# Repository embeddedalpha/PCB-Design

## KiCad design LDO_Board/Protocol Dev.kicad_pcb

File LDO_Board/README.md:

# LDO-Board

#1 View 1

#2 View 2

#3 View 3

#4 F.Cu

#5 B.Cu

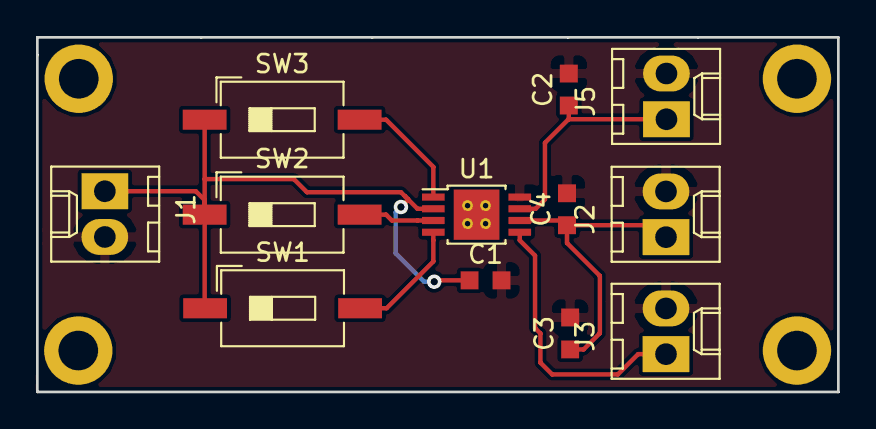
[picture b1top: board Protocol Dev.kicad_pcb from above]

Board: 2 copper layers, 44.5 x 19.7 mm, 12 parts (0 on the bottom side), 8 nets.

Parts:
C1, C2, C3, C4: C_Small; C_0603_1608Metric_Pad0.99x1.00mm_HandSolder
J1, J2, J3, J5: Conn_01x02; Molex_KK-6410-02_02x2.54mm_Straight
SW1, SW2, SW3: SW_Push; SW_DIP_SPSTx01_Slide_6.7x4.1mm_W8.61mm_P2.54mm_LowProfile
U1: MIC5356-SGYMME; MSOP-8-1EP_3x3mm_P0.65mm_EP2.54x2.8mm_ThermalVias

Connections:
+1V5: C3.1, C4.1, J2.1, U1.6
+1V8: C2.1, J5.1, U1.7
+3V3: J3.1, U1.5
/EN1: SW1.2, U1.4
/EN2: SW2.2, U1.3
/EN3: SW3.2, U1.1
/IN: C1.1, J1.1, SW1.1, SW2.1, SW3.1, U1.2
GND: C1.2, C2.2, C3.2, C4.2, J1.2, J2.2, J3.2, J5.2, U1.8

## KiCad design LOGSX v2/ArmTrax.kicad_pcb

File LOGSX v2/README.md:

<H1> LOGSX v2: Low Power Logistic Tracker </H1>

<H4> Overview </H4>

<H4> 1: </H4>

<H4> 2: </H4>

<H4> 3: </H4>

<H4> 4: </H4>

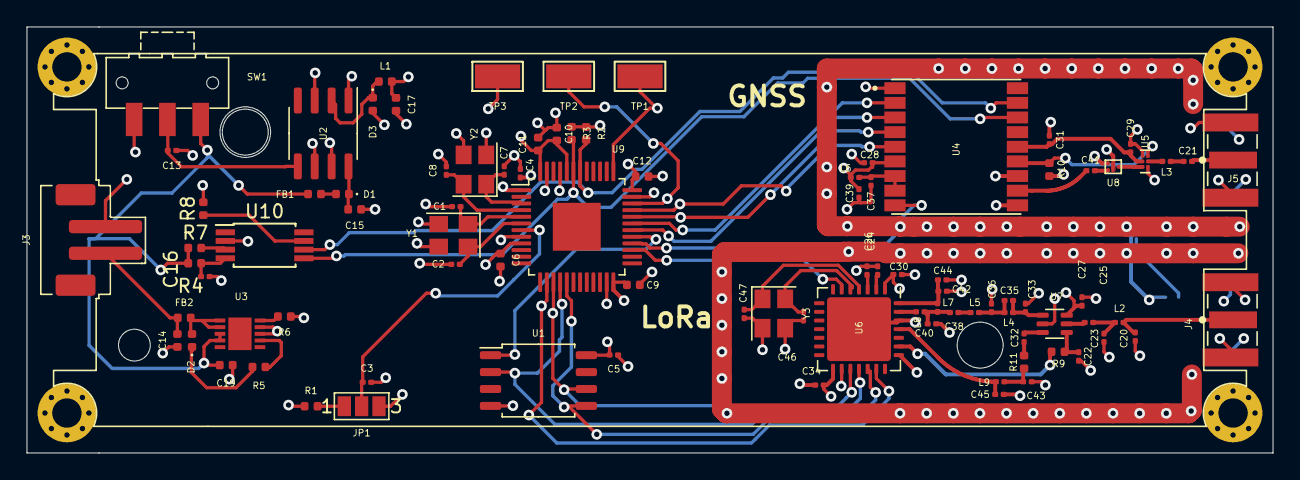
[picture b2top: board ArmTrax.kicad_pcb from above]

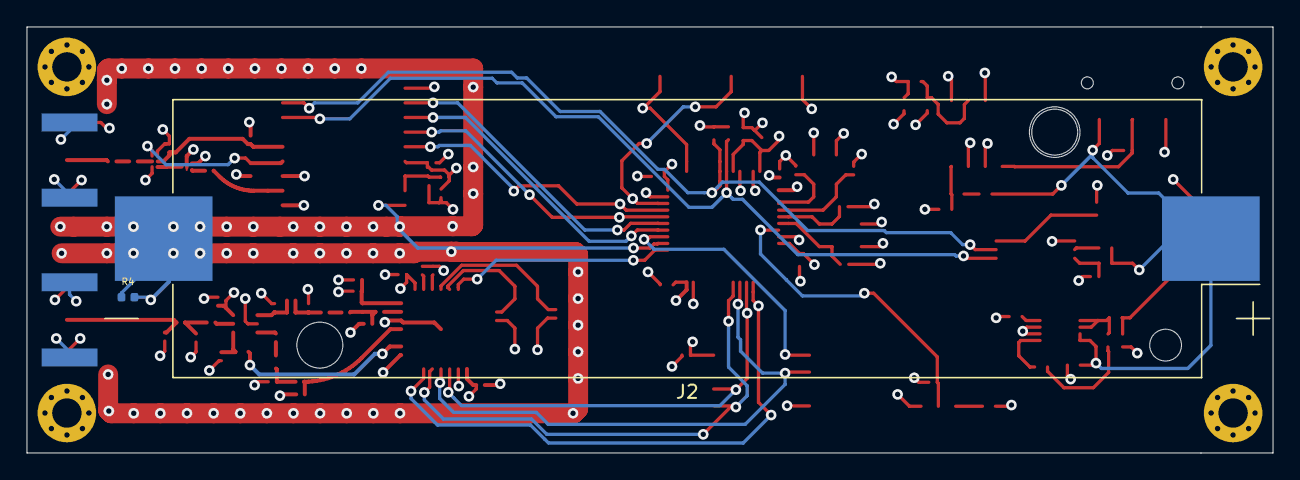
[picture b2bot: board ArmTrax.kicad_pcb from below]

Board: 4 copper layers, 93.6 x 32.0 mm, 94 parts (2 on the bottom side), 63 nets.

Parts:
C1, C2, C3, C4, C5, C46, C47: 2.2pF; C_0201_0603Metric
C6, C15: 1uF; C_0402_1005Metric
C7, C8: 1pF; C_0201_0603Metric
C9, C10, C11, C12: 2.2pF; C_0402_1005Metric
C13, C16, C22, C27, C29: 1nF; C_0201_0603Metric
C14, C19: 22pF; C_0402_1005Metric
C17: 330uF; C_0402_1005Metric
C20, C23, C25, C33, C35, C36, C38, C40, C42, C43, C44, C45: X; C_0201_0603Metric
C21, C32, C41: 120pF; C_0201_0603Metric
C24, C26, C30, C34: 100nF; C_0201_0603Metric
C28, C31, C37, C39: 56pF; C_0201_0603Metric
D1: D_Small; D_0402_1005Metric
D2: LED; LED_0402_1005Metric
D3: 1N5822; D_0402_1005Metric
FB1, FB2: 100MHz; L_0402_1005Metric
J2: BATTERY CONN; BatteryHolder_Keystone_1042_1x18650
J3: POWER IN; JST_PH_B2B-PH-SM4-TB_1x02-1MP_P2.00mm_Vertical
J4, J5: SMA_Edge; SMA-J-P-H-ST-EM1
JP1: SolderJumper_3_Open; SolderJumper-3_P1.3mm_Open_Pad1.0x1.5mm_NumberLabels
L1: 330uH; L_0402_1005Metric
L2, L4, L5, L7, L8, L9: X; L_0201_0603Metric
L3: 5nF; L_0201_0603Metric
L6: 27nH; L_0201_0603Metric
R1: 1K7; R_0402_1005Metric
R2, R3: 4.7K; R_0402_1005Metric
R4: 500; R_0402_1005Metric
R4#2: R_Small; R_0402_1005Metric
R5, R6, R7, R8, R9: 1K; R_0402_1005Metric
R10: 10K; R_0402_1005Metric
R11: 0; R_0402_1005Metric
SW1: SW_SPDT; SW_SPDT_CK-JS102011SAQN
TP1, TP2, TP3: TestPoint; TestPoint_Keystone_5015_Micro-Minature
U1: W25Q32JVSS; SOIC-8_5.23x5.23mm_P1.27mm
U2: LT1129-3.3_SO8; SOIC-8_3.9x4.9mm_P1.27mm
U3: MCP73113_4; MCP73113
U4: TESEO-LIV3F
U5: BGA725L6E6327FTSA1
U6: SX1273; QFN-28-1EP_6x6mm_P0.65mm_EP4.8x4.8mm
U7: PE4259; PE4259_sc70
U8: B4327
U9: STM32F103C8Tx; LQFP-48-1EP_7x7mm_P0.5mm_EP3.6x3.6mm
U10: DS2782; TSSOP-8_4.4x3mm_P0.65mm
Y1, Y2, Y3: Crystal_GND23; Crystal_SMD_Abracon_ABM8G-4Pin_3.2x2.5mm

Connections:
1PPS: U4.4, U9.32
+3V3: C4.2, C5.2, C6.1, C9.1, C10.1, C11.1, C12.1, C17.1, C27.2, C28.2, C30.2, C34.2, C39.2, L1.2, L6.2, R1.1, R2.1, R3.1, U1.8, U2.1, U4.6, U6.1, U6.15, U7.6, U9.1, U9.9, U9.24, U9.36, U9.44, U9.48
ANT_OFF: R10.1, U4.13, U5.6
BATTERY: C19.1, FB1.2, J2.1, R4.2, R7.2, SW1.1, U3.3, U3.4
FLASH_NSS: U1.1, U9.29
GND: C1.2, C2.2, C3.2, C4.1, C5.1, C6.2, C7.2, C8.2, C9.2, C10.2, C11.2, C12.2, C13.2, C14.2, C15.2, C16.2, C17.2, C19.2, C20.1, C22.2, C23.2, C24.2, C26.2, C27.1, C28.1, C29.1, C30.1, C31.1, C33.1, C34.1, C36.1, C37.1, C39.1, C40.2, C42.2, C43.1, C44.2, C45.1, C46.2, C47.2, D3.2, J2.2, J3.2, J4.2_1, J4.2_2, J4.3_1, J4.3_2, J5.2_1, J5.2_2, J5.3_1, J5.3_2, JP1.3, R4#2.1, R4#2.2, R6.1, R8.2, R10.2, SW1.3, TP3.1, U1.4, U2.3, U2.6, U2.7, U3.8, U3.9, U4.1, U4.9, U4.10, U4.12, U5.1, U5.4, U6.16, U6.22, U6.26, U6.29, U7.2, U8.2, U8.3, U8.5, U9.8, U9.23, U9.28, U9.35, U9.47, U10.2, Y1.2, Y1.3, Y2.2, Y2.3, Y3.2, Y3.3
LoRa_NSS: U6.20, U9.14
LoRa_RESET: U6.6, U9.27
MISO: U1.2, U6.18, U9.16
MOSI: U1.5, U6.19, U9.17
unnamed: C3.1, JP1.2, U9.7
unnamed: C13.1, SW1.2, U2.5
unnamed: C14.1, FB2.2, J3.1
unnamed: C15.1, D1.1, U2.8
unnamed: C16.1, R4.1, U10.4
unnamed: C20.2, J4.1, L2.1
unnamed: C21.1, L3.1
unnamed: C21.2, J5.1
unnamed: C22.1, R9.1, U7.4
unnamed: C23.1, C25.2, L2.2
unnamed: C24.1, U6.2
unnamed: C25.1, U7.5
unnamed: C26.1, U6.3
unnamed: C32.1, U7.3
unnamed: C32.2, R11.2
unnamed: C33.2, C35.1, L4.1, U7.1
unnamed: C35.2, C36.2, L4.2, L5.1
unnamed: C37.2, L6.1, U4.7, U4.8
unnamed: C38.1, L5.2
unnamed: C38.2, C40.1, L7.1, L8.1
unnamed: C41.2, U8.4
unnamed: C43.2, L9.1, R11.1
unnamed: D1.2, FB1.1
unnamed: D2.1, R5.1
unnamed: D2.2, FB2.1, U3.1, U3.2
unnamed: D3.1, L1.1, U2.2
unnamed: JP1.1, R1.2
unnamed: L3.2, U5.5
unnamed: R5.2, U3.7
unnamed: R6.2, U3.10
unnamed: R7.1, U10.3
unnamed: U5.3, U8.1
OSC32_IN: C7.1, U9.3, Y2.1
OSC32_OUT: C8.1, U9.4, Y2.4
OSC_IN: C1.1, U9.5, Y1.1
OSC_OUT: C2.1, U9.6, Y1.4
PA_BOOST: L8.2, U6.27
RFI: C45.2, L9.2, U6.25
RF_IN: C41.1, U4.11
RX: U4.3, U9.30
RXTX: R9.2, U6.23
SCK: U1.6, U6.17, U9.15
SCL: R2.2, U4.17, U9.42, U10.6
SDA: R3.2, U4.16, U9.43, U10.5
SNS: R8.1, U10.7
SWCLK: TP1.1, U9.37
SWDIO: TP2.1, U9.34
TX: U4.2, U9.31
VCC_RF: C29.2, C31.2, U4.14, U5.2
VR_PA: C42.1, C44.1, L7.2, U6.28
WAKE_UP: U4.5, U9.33
XTA: C47.1, U6.4, Y3.1
XTB: C46.1, U6.5, Y3.4

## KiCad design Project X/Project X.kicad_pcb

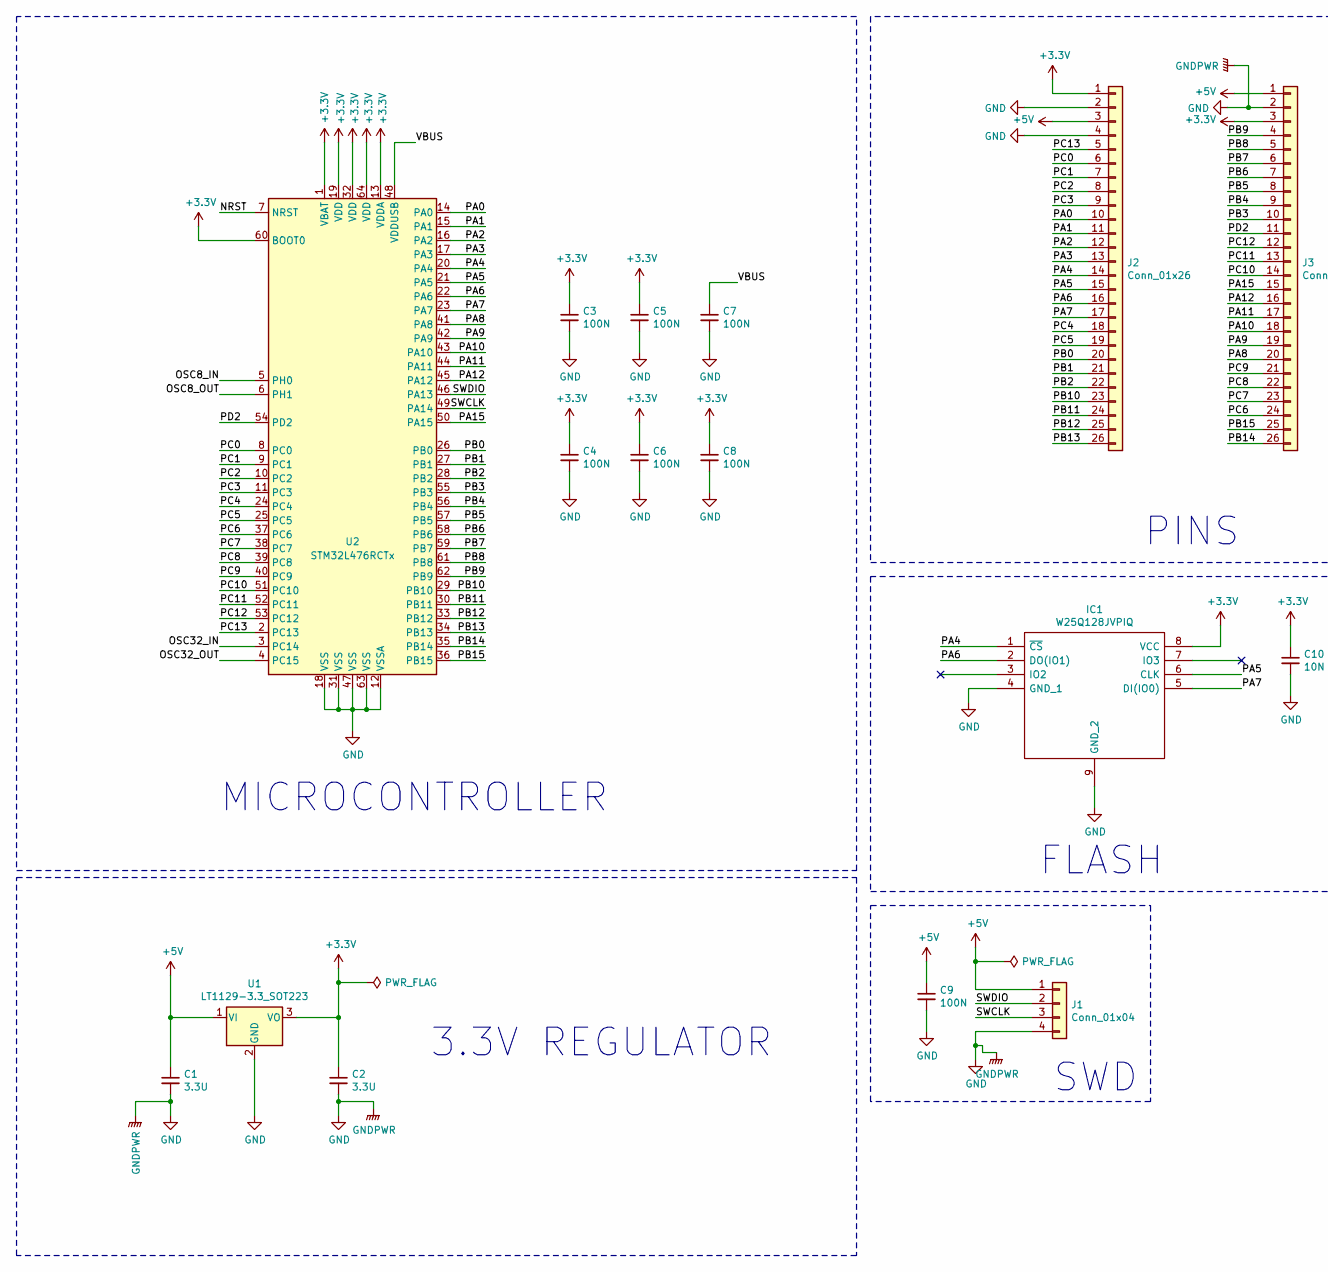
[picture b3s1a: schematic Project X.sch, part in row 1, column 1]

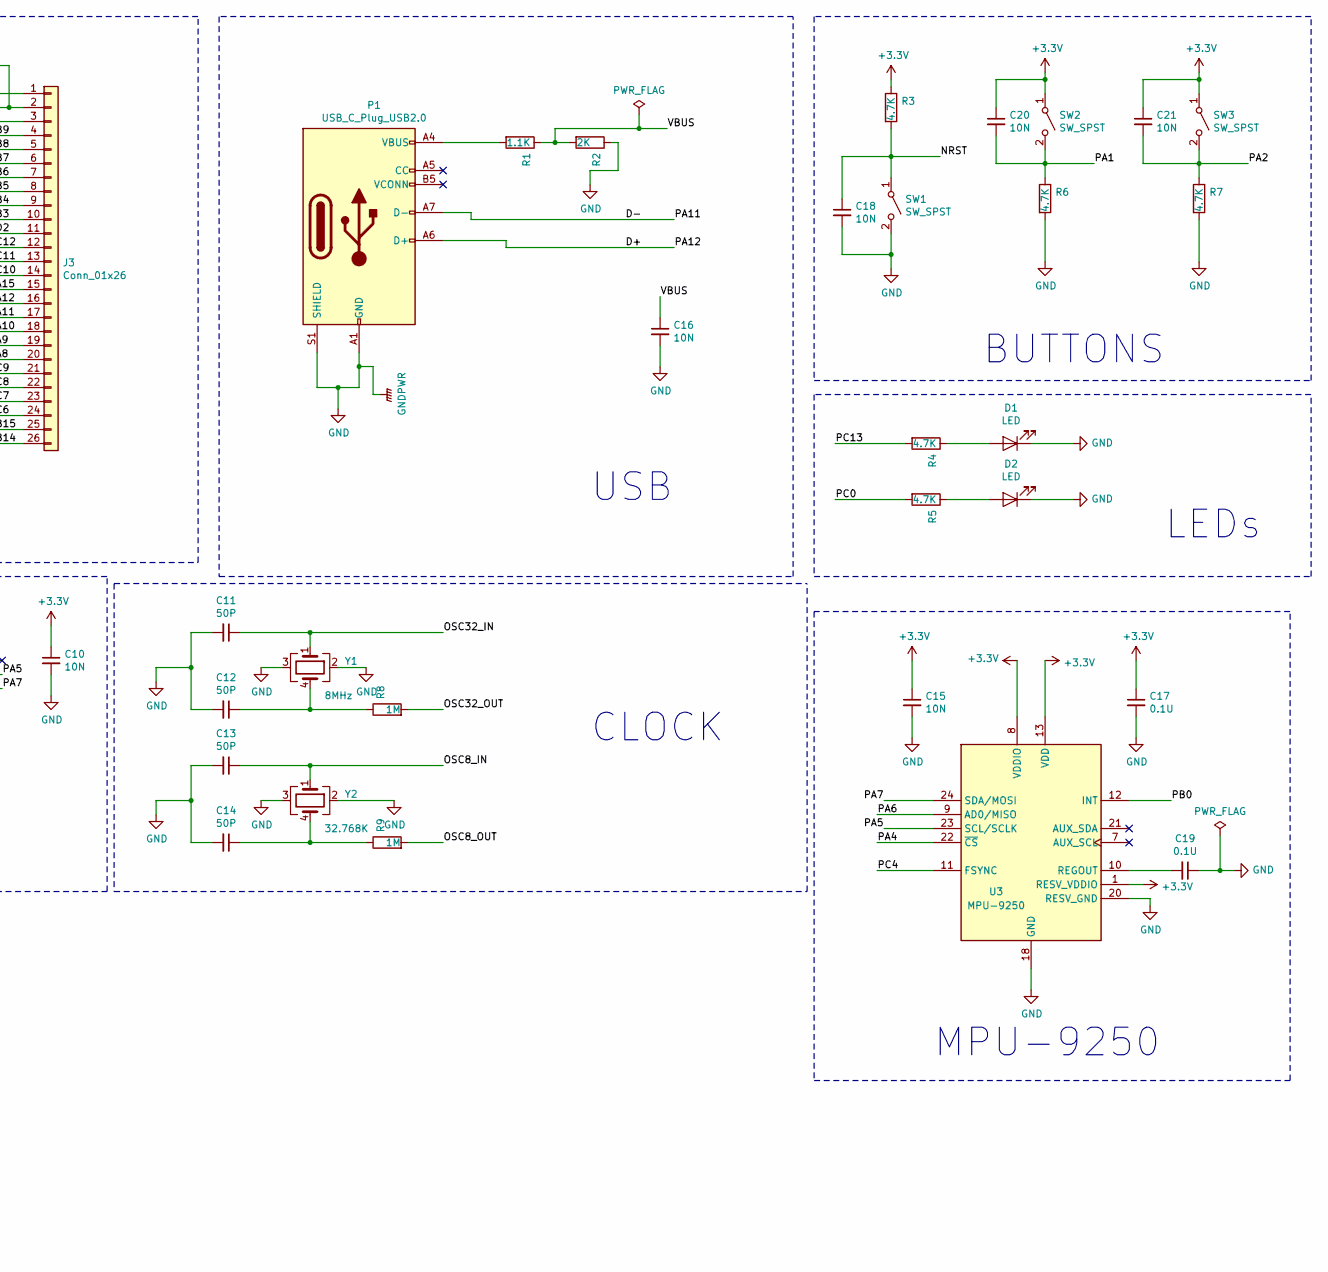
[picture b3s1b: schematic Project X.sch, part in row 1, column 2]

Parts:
C1, C2: 3.3U; CP_EIA-1608-08_AVX-J
C3, C4, C5, C6, C7, C8, C9: 100N; C_0201_0603Metric
C10, C15, C16, C18, C20, C21: 10N; C_0201_0603Metric
C11, C12, C13, C14: 50P; C_0201_0603Metric
C17, C19: 0.1U; C_0201_0603Metric
D1, D2: LED; LED_0402_1005Metric
IC1: W25Q128JVPIQ; WSON-8-1EP_6x5mm_P1.27mm_EP3.4x4mm; Mouser Part Number 454-W25Q128JVPIQ
J1: Conn_01x04; PinHeader_1x04_P2.54mm_Horizontal
J2, J3: Conn_01x26; PinHeader_1x26_P2.54mm_Vertical
P1: USB_C_Plug_USB2.0; USB_C_Receptacle_HRO_TYPE-C-31-M-12
R1: 1.1K; R_0402_1005Metric
R2: 2K; R_0402_1005Metric
R3, R4, R5, R6, R7: 4.7K; R_0402_1005Metric
R8, R9: 1M; R_0402_1005Metric
SW1, SW2, SW3: SW_SPST; SW_PUSH_6mm_H5mm
U1: LT1129-3.3_SOT223; SOT-223-3_TabPin2
U2: STM32L476RCTx; LQFP-64_10x10mm_P0.5mm
U3: MPU-9250; QFN-24-1EP_4x4mm_P0.5mm_EP2.6x2.6mm_ThermalVias
Y1: 8MHz; Crystal_SMD_3225-4Pin_3.2x2.5mm
Y2: 32.768K; Crystal_SMD_3225-4Pin_3.2x2.5mm

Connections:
+3V3: C2.1, C3.1, C4.1, C5.1, C6.1, C8.1, C10.1, C15.1, C17.1, C20.1, C21.1, IC1.8 (VCC), J2.1, J3.3, R3.1, SW2.1 (A), SW3.1 (A), U1.3 (VO), U2.1 (VBAT), U2.13 (VDDA), U2.19 (VDD), U2.32 (VDD), U2.60 (BOOT0), U2.64 (VDD), U3.1 (RESV_VDDIO), U3.8 (VDDIO), U3.13 (VDD); also elsewhere on the board
+5V: C1.1, C9.1, J1.1, J2.3, J3.1, U1.1 (VI)
/D+: J3.16, P1.A6 (D+), U2.45 (PA12)
/D-: J3.17, P1.A7 (D-), U2.44 (PA11)
/NRST: C18.1, R3.2, SW1.1 (A), U2.7 (NRST)
/OSC8_IN: C13.1, U2.5 (PH0), Y2.1
/OSC8_OUT: R9.2, U2.6 (PH1)
/OSC32_IN: C11.1, U2.3 (PC14), Y1.1
/OSC32_OUT: R8.2, U2.4 (PC15)
/PA0: J2.10, U2.14 (PA0)
/PA1: C20.2, J2.11, R6.1, SW2.2 (B), U2.15 (PA1); also elsewhere on the board
/PA2: C21.2, J2.12, R7.1, SW3.2 (B), U2.16 (PA2); also elsewhere on the board
/PA3: J2.13, U2.17 (PA3)
/PA4: IC1.1 (~CS), J2.14, U2.20 (PA4), U3.22 (~CS)
/PA5: IC1.6 (CLK), J2.15, U2.21 (PA5), U3.23 (SCL/SCLK)
/PA6: IC1.2 (DO(IO1)), J2.16, U2.22 (PA6), U3.9 (AD0/MISO)
/PA7: IC1.5 (DI(IO0)), J2.17, U2.23 (PA7), U3.24 (SDA/MOSI)
/PA8: J3.20, U2.41 (PA8)
/PA9: J3.19, U2.42 (PA9)
/PA10: J3.18, U2.43 (PA10)
/PA15: J3.15, U2.50 (PA15)
/PB0: J2.20, U2.26 (PB0), U3.12 (INT)
/PB1: J2.21, U2.27 (PB1)
/PB2: J2.22, U2.28 (PB2)
/PB3: J3.10, U2.55 (PB3)
/PB4: J3.9, U2.56 (PB4)
/PB5: J3.8, U2.57 (PB5)
/PB6: J3.7, U2.58 (PB6)
/PB7: J3.6, U2.59 (PB7)
/PB8: J3.5, U2.61 (PB8)
/PB9: J3.4, U2.62 (PB9)
/PB10: J2.23, U2.29 (PB10)
/PB11: J2.24, U2.30 (PB11)
/PB12: J2.25, U2.33 (PB12)
/PB13: J2.26, U2.34 (PB13)
/PB14: J3.26, U2.35 (PB14)
/PB15: J3.25, U2.36 (PB15)
/PC0: J2.6, R5.2, U2.8 (PC0)
/PC1: J2.7, U2.9 (PC1)
/PC2: J2.8, U2.10 (PC2)
/PC3: J2.9, U2.11 (PC3)
/PC4: J2.18, U2.24 (PC4), U3.11 (FSYNC)
/PC5: J2.19, U2.25 (PC5)
/PC6: J3.24, U2.37 (PC6)
/PC7: J3.23, U2.38 (PC7)
/PC8: J3.22, U2.39 (PC8)
/PC9: J3.21, U2.40 (PC9)
/PC10: J3.14, U2.51 (PC10)
/PC11: J3.13, U2.52 (PC11)
/PC12: J3.12, U2.53 (PC12)
/PC13: J2.5, R4.2, U2.2 (PC13)
/PD2: J3.11, U2.54 (PD2)
/SWCLK: J1.3, U2.49 (PA14)
/SWDIO: J1.2, U2.46 (PA13)
/VBUS: C7.1, C16.1, R1.1, R2.2, U2.48 (VDDUSB)
GND: C1.2, C2.2, C3.2, C4.2, C5.2, C6.2, C7.2, C8.2, C9.2, C10.2, C11.2, C12.2, C13.2, C14.2, C15.2, C16.2, C17.2, C18.2, C19.1, D1.1 (K), D2.1 (K), IC1.4 (GND_1), IC1.9 (GND_2), J1.4, J2.2, J2.4, J3.2, P1.A1 (GND), P1.A12 (GND), P1.B1 (GND), P1.B12 (GND), P1.S1 (SHIELD), R2.1, R6.2, R7.2, SW1.2 (B), U1.2 (GND), U2.12 (VSSA), U2.18 (VSS), U2.31 (VSS), U2.47 (VSS), U2.63 (VSS), U3.18 (GND), U3.20 (RESV_GND), Y1.2, Y1.3, Y2.2, Y2.3
unnamed: C12.1, R8.1, Y1.4
unnamed: C14.1, R9.1, Y2.4
unnamed: C19.2, U3.10 (REGOUT)
unnamed: D1.2 (A), R4.1
unnamed: D2.2 (A), R5.1
unnamed: P1.A4 (VBUS), P1.A9 (VBUS), P1.B4 (VBUS), P1.B9 (VBUS), R1.2

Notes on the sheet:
MICROCONTROLLER
BUTTONS
FLASH
SWD
CLOCK
MPU-9250
USB
PINS
LEDs
3.3V REGULATOR

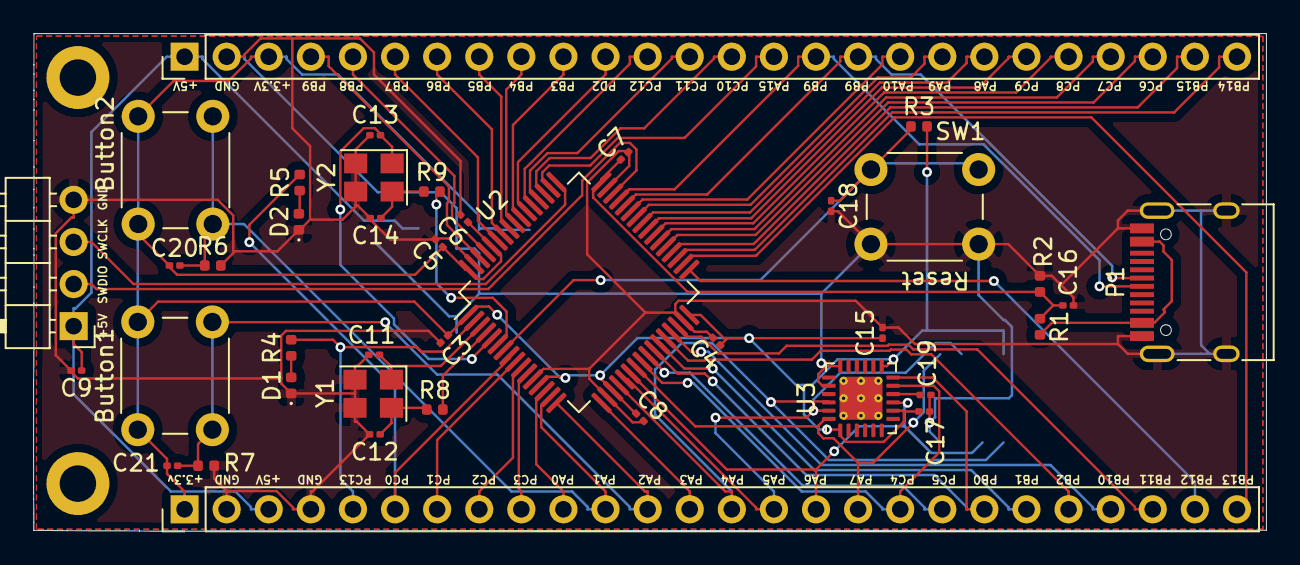
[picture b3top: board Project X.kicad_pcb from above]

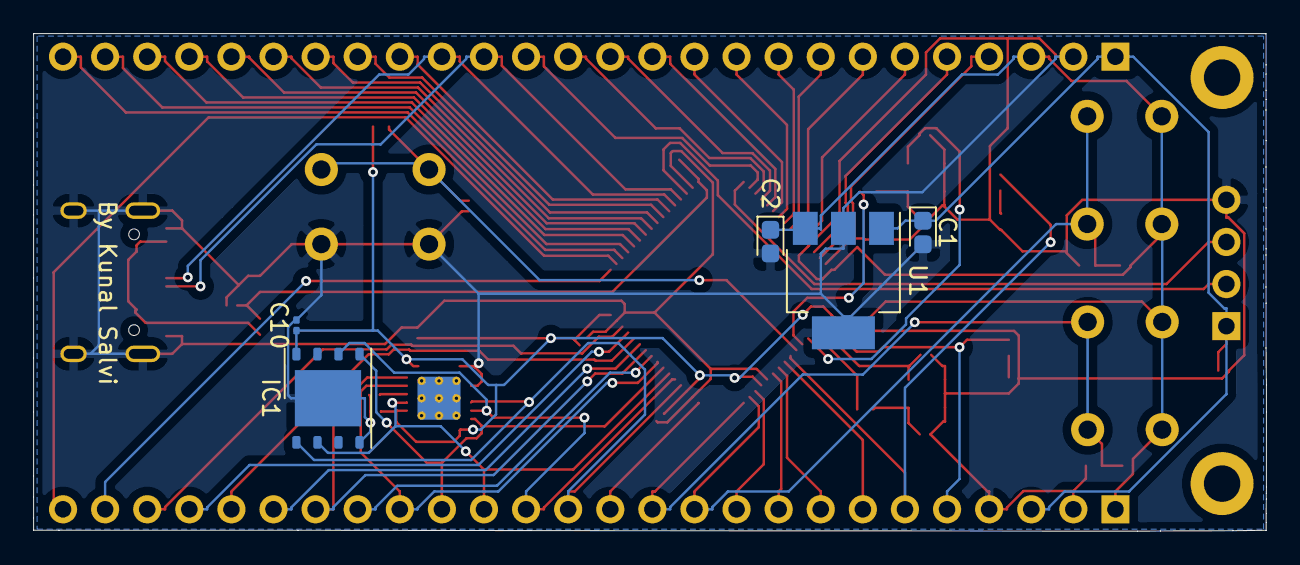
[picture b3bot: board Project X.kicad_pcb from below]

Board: 2 copper layers, 74.4 x 30.0 mm, 46 parts (5 on the bottom side), 62 nets.

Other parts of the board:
Button1, Button2: SW_SPST; SW_PUSH_6mm_H5mm
mouse-bite-2mm-slot: VAL**; mouse-bite-2mm-slot

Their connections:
+3V3: Button1.1, Button2.1; also elsewhere on the board
/PA1: Button2.2; also elsewhere on the board
/PA2: Button1.2; also elsewhere on the board

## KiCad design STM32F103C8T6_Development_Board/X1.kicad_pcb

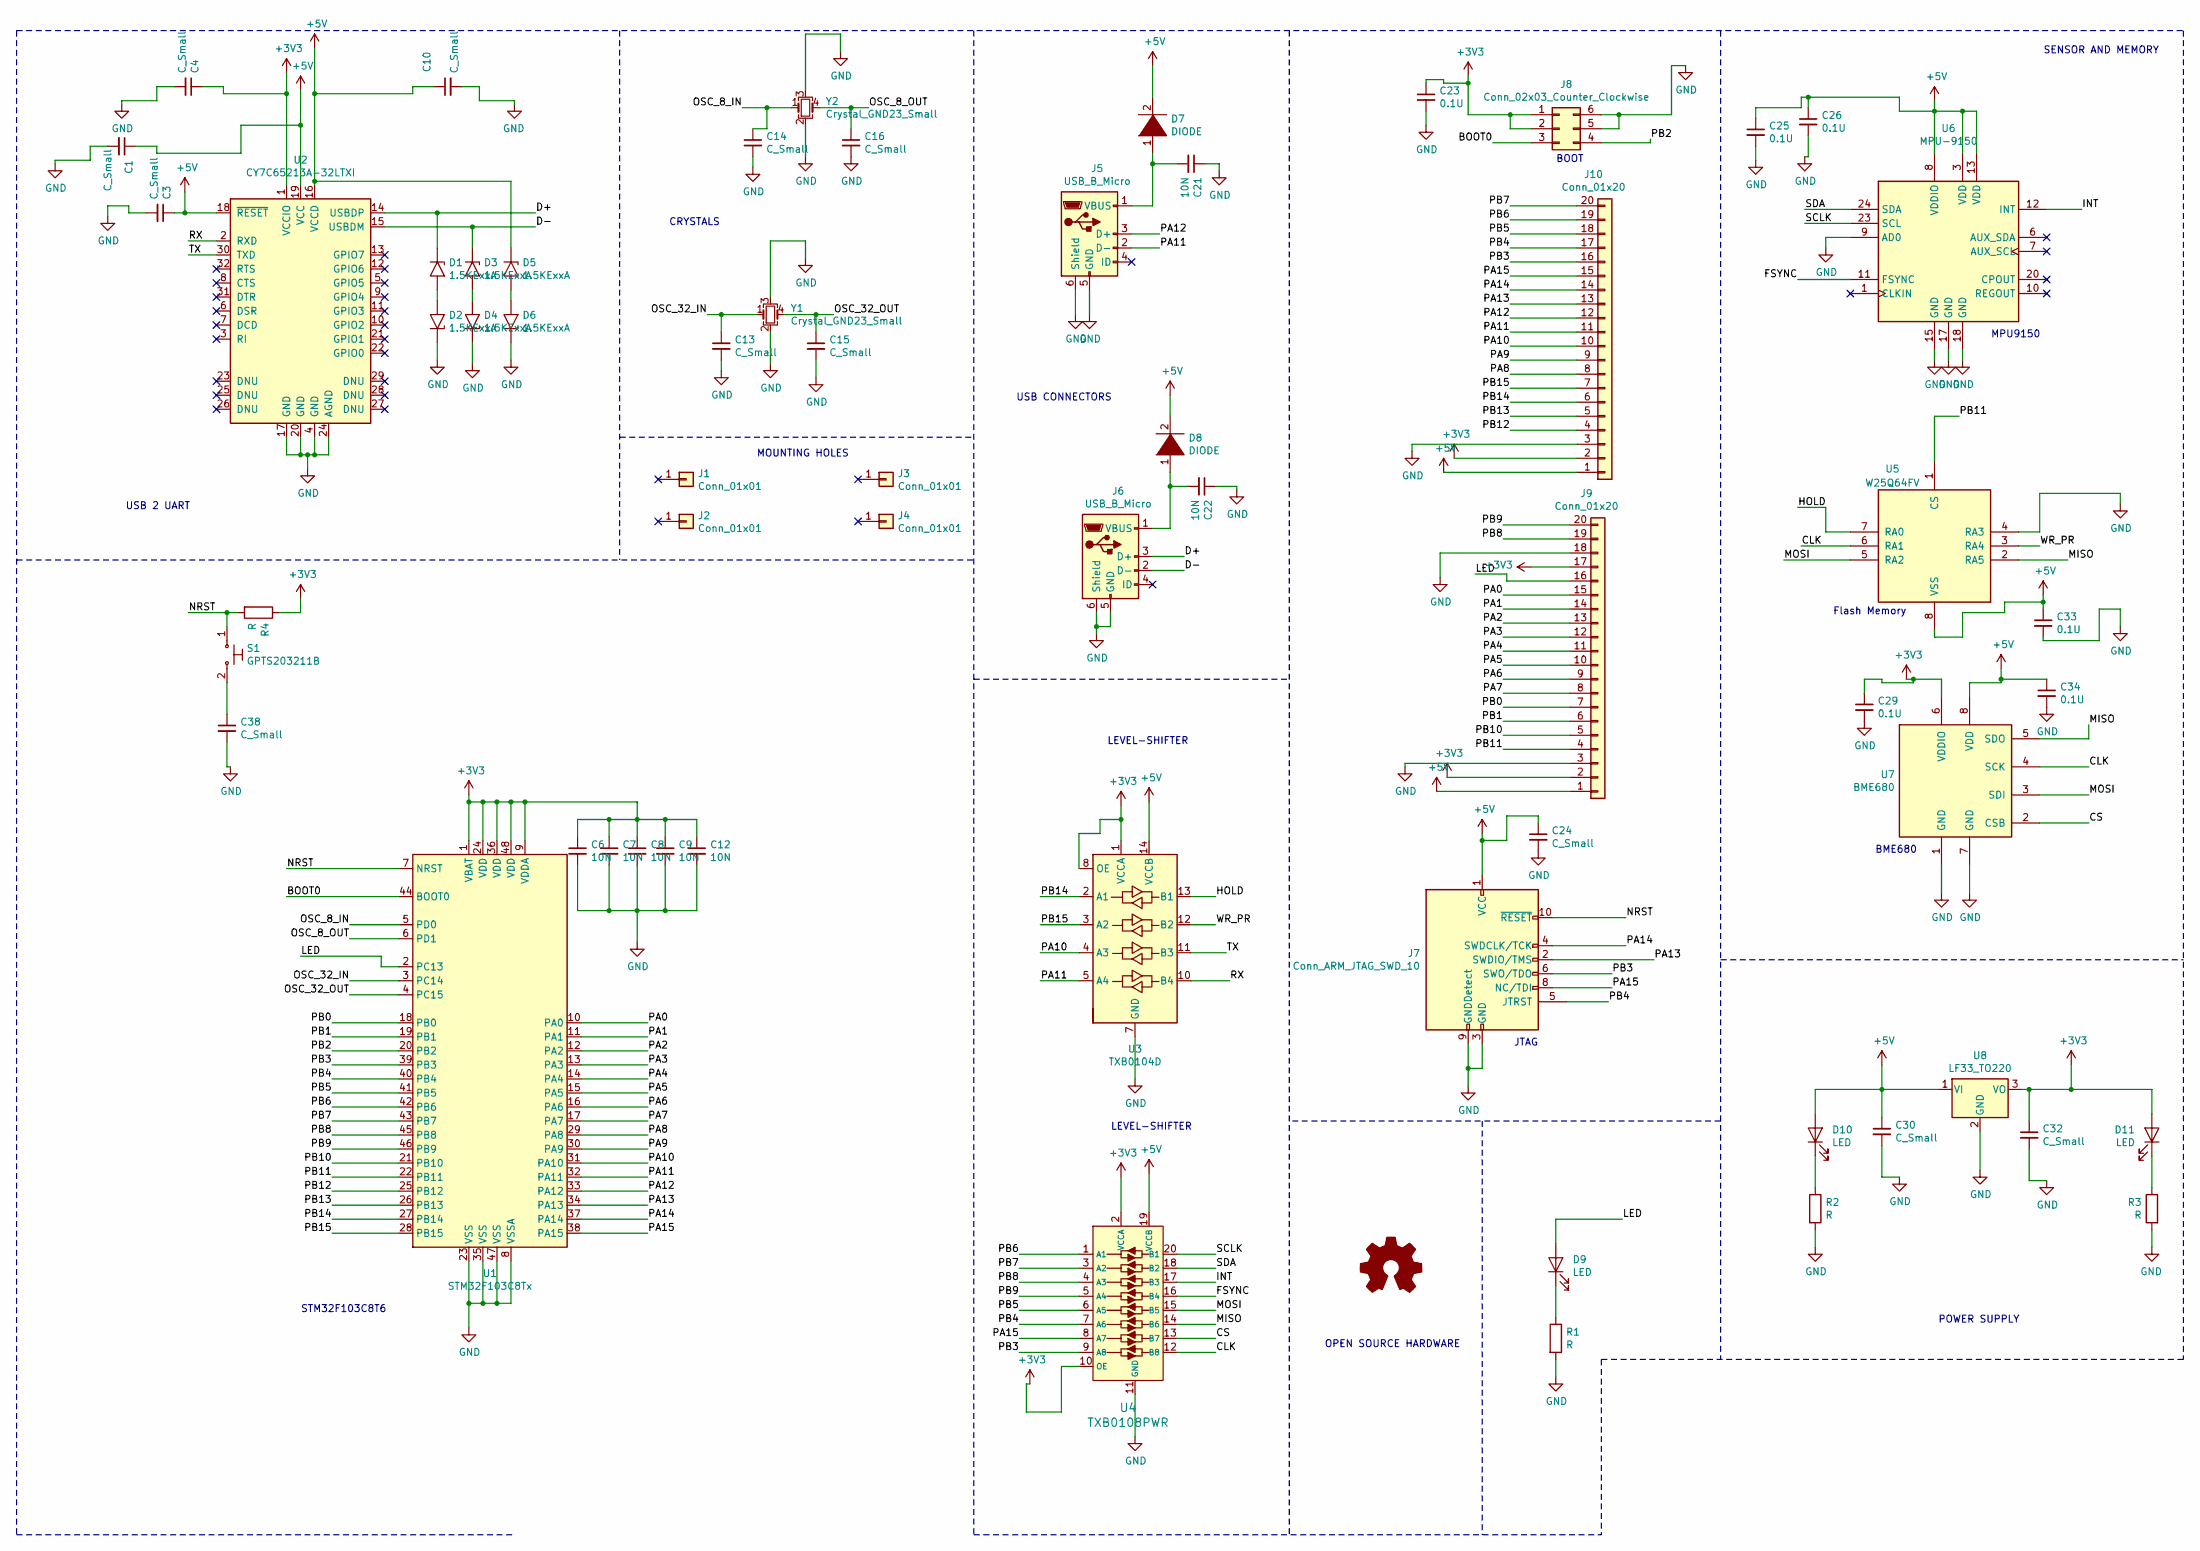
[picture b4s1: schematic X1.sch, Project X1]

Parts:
C1, C3, C4, C10, C13, C14, C15, C16, C24, C30, C32, C38: C_Small; C_0201_0603Metric
C6, C7, C8, C9, C12, C21, C22: 10N; C_0201_0603Metric
C23, C25, C26, C29, C33, C34: 0.1U; C_0201_0603Metric
D1, D2, D3, D4, D5, D6: 1.5KExxA; R_0201_0603Metric
D7, D8: DIODE; R_0201_0603Metric
D9, D10, D11: LED; LED_0201_0603Metric
J1, J2, J3, J4: Conn_01x01; MountingHole_3.2mm_M3_ISO14580_Pad
J5, J6: USB_B_Micro; USB_Micro-B_Molex_47346-0001
J7: Conn_ARM_JTAG_SWD_10; PinHeader_2x05_P2.54mm_Vertical
J8: Conn_02x03_Counter_Clockwise; PinHeader_2x03_P2.54mm_Vertical
J9, J10: Conn_01x20; PinHeader_1x20_P2.54mm_Vertical
R1, R2, R3, R4: R; R_0201_0603Metric
S1: GPTS203211B; SW_SPST_TL3342; MPN GPTS203211B; Digi-Key_PN CW181-ND
U1: STM32F103C8Tx; LQFP-48_7x7mm_P0.5mm
U2: CY7C65213A-32LTXI; LQFP-32-1EP_5x5mm_P0.5mm_EP3.45x3.45mm
U3: TXB0104D; SOIC-14_3.9x8.7mm_P1.27mm
U4: TXB0108PWR; TSSOP-20_W4.4mm; MPN TXB0108PWR; Digi-Key_PN 296-21527-1-ND
U5: W25Q64FV; SOIC-8_3.9x4.9mm_P1.27mm
U6: MPU-9150; QFN-24-1EP_3x3mm
U7: BME680; Bosch_LGA-8_3x3mm_P0.8mm_ClockwisePinNumbering
U8: LF33_TO220; SOT-23
Y1, Y2: Crystal_GND23_Small; Crystal_SMD_3225-4Pin_3.2x2.5mm_HandSoldering

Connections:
+3V3: C4.1, C6.1, C7.1, C8.1, C9.1, C12.1, C23.1, C29.1, C32.1, D11.2 (A), J8.1, J8.2, J9.2, J9.17, J10.2, R4.1, U1.1 (VBAT), U1.9 (VDDA), U1.24 (VDD), U1.36 (VDD), U1.48 (VDD), U2.1 (VCCIO), U3.1 (VCCA), U3.8 (OE), U4.2 (VCCA), U4.10 (OE), U7.6 (VDDIO), U8.3 (VO)
+5V: C1.1, C3.1, C10.1, C24.1, C25.1, C26.1, C30.1, C33.1, C34.1, D5.1 (A1), D7.2 (A), D8.2 (A), D10.2 (A), J7.1 (VCC), J9.1, J10.1, U2.16 (VCCD), U2.18 (~RESET), U2.19 (VCC), U3.14 (VCCB), U4.19 (VCCB), U5.8 (VSS), U6.3 (VDD), U6.8 (VDDIO), U6.13 (VDD), U7.8 (VDD), U8.1 (VI)
/BOOT0: J8.3, U1.44 (BOOT0)
/CLK: U4.12 (B8), U5.6 (RA1), U7.4 (SCK)
/CS: U4.13 (B7), U7.2 (CSB)
/D+: D1.1 (A1), J6.3 (D+), U2.14 (USBDP)
/D-: D3.1 (A1), J6.2 (D-), U2.15 (USBDM)
/FSYNC: U4.16 (B4), U6.11 (FSYNC)
/HOLD: U3.13 (B1), U5.7 (RA0)
/INT: U4.17 (B3), U6.12 (INT)
/LED: D9.2 (A), J9.16, U1.2 (PC13)
/MISO: U4.14 (B6), U5.2 (RA5), U7.5 (SDO)
/MOSI: U4.15 (B5), U5.5 (RA2), U7.3 (SDI)
/NRST: J7.10 (~RESET~), R4.2, S1.1, U1.7 (NRST)
/OSC_8_IN: C14.1, U1.5 (PD0), Y2.1
/OSC_8_OUT: C16.1, U1.6 (PD1), Y2.4
/OSC_32_IN: C13.1, U1.3 (PC14), Y1.1
/OSC_32_OUT: C15.1, U1.4 (PC15), Y1.4
/PA0: J9.15, U1.10 (PA0)
/PA1: J9.14, U1.11 (PA1)
/PA2: J9.13, U1.12 (PA2)
/PA3: J9.12, U1.13 (PA3)
/PA4: J9.11, U1.14 (PA4)
/PA5: J9.10, U1.15 (PA5)
/PA6: J9.9, U1.16 (PA6)
/PA7: J9.8, U1.17 (PA7)
/PA8: J10.8, U1.29 (PA8)
/PA9: J10.9, U1.30 (PA9)
/PA10: J10.10, U1.31 (PA10), U3.4 (A3)
/PA11: J5.2 (D-), J10.11, U1.32 (PA11), U3.5 (A4)
/PA12: J5.3 (D+), J10.12, U1.33 (PA12)
/PA13: J7.2 (SWDIO/TMS), J10.13, U1.34 (PA13)
/PA14: J7.4 (SWDCLK/TCK), J10.14, U1.37 (PA14)
/PA15: J7.8 (NC/TDI), J10.15, U1.38 (PA15), U4.8 (A7)
/PB0: J9.7, U1.18 (PB0)
/PB1: J9.6, U1.19 (PB1)
/PB2: J8.4, U1.20 (PB2)
/PB3: J7.6 (SWO/TDO), J10.16, U1.39 (PB3), U4.9 (A8)
/PB5: J10.18, U1.41 (PB5), U4.6 (A5)
/PB6: J10.19, U1.42 (PB6), U4.1 (A1)
/PB7: J10.20, U1.43 (PB7), U4.3 (A2)
/PB8: J9.19, U1.45 (PB8), U4.4 (A3)
/PB9: J9.20, U1.46 (PB9), U4.5 (A4)
/PB10: J9.5, U1.21 (PB10)
/PB11: J9.4, U1.22 (PB11), U5.1 (CS)
/PB12: J10.4, U1.25 (PB12)
/PB13: J10.5, U1.26 (PB13)
/PB14: J10.6, U1.27 (PB14), U3.2 (A1)
/PB15: J10.7, U1.28 (PB15), U3.3 (A2)
/RX: U2.2 (RXD), U3.10 (B4)
/SCLK: U4.20 (B1), U6.23 (SCL)
/SDA: U4.18 (B2), U6.24 (SDA)
/TX: U2.30 (TXD), U3.11 (B3)
/WR_PR: U3.12 (B2), U5.3 (RA4)
unnamed: C21.2, D7.1 (K), J5.1 (VBUS)
unnamed: C22.2, D8.1 (K), J6.1 (VBUS)
unnamed: C38.1, S1.2
unnamed: D1.2 (A2), D2.2 (A2)
unnamed: D3.2 (A2), D4.2 (A2)
unnamed: D5.2 (A2), D6.2 (A2)
unnamed: D9.1 (K), R1.1
unnamed: D10.1 (K), R2.1
unnamed: D11.1 (K), R3.1

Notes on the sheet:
BOOT
MPU9150
LEVEL-SHIFTER
JTAG
Flash Memory
BME680
SENSOR AND MEMORY
OPEN SOURCE HARDWARE
POWER SUPPLY
USB 2 UART
MOUNTING HOLES
CRYSTALS
USB CONNECTORS
STM32F103C8T6

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
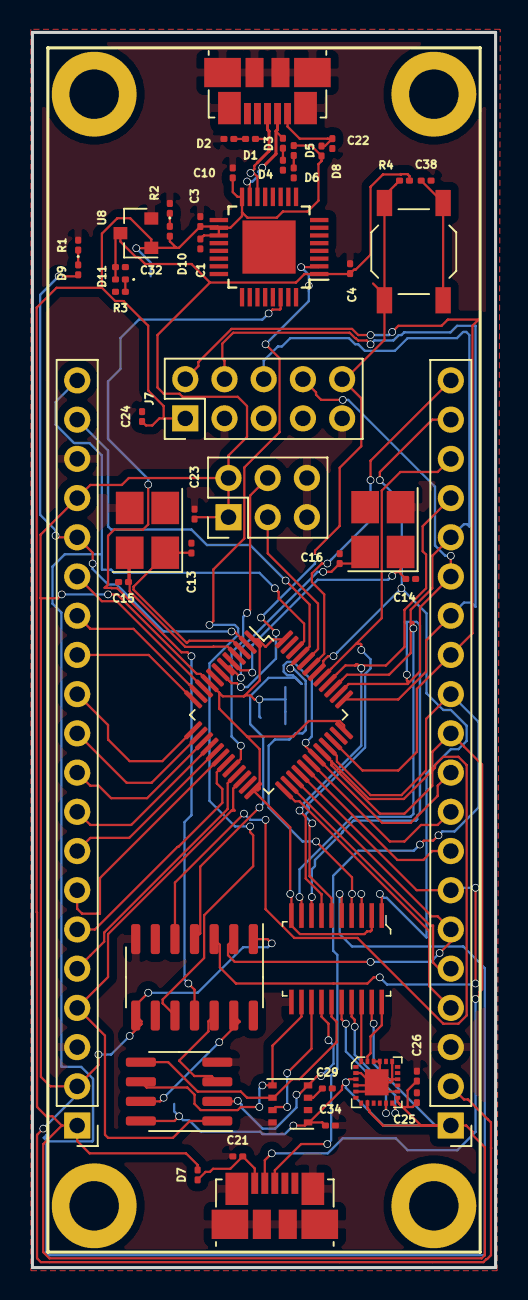
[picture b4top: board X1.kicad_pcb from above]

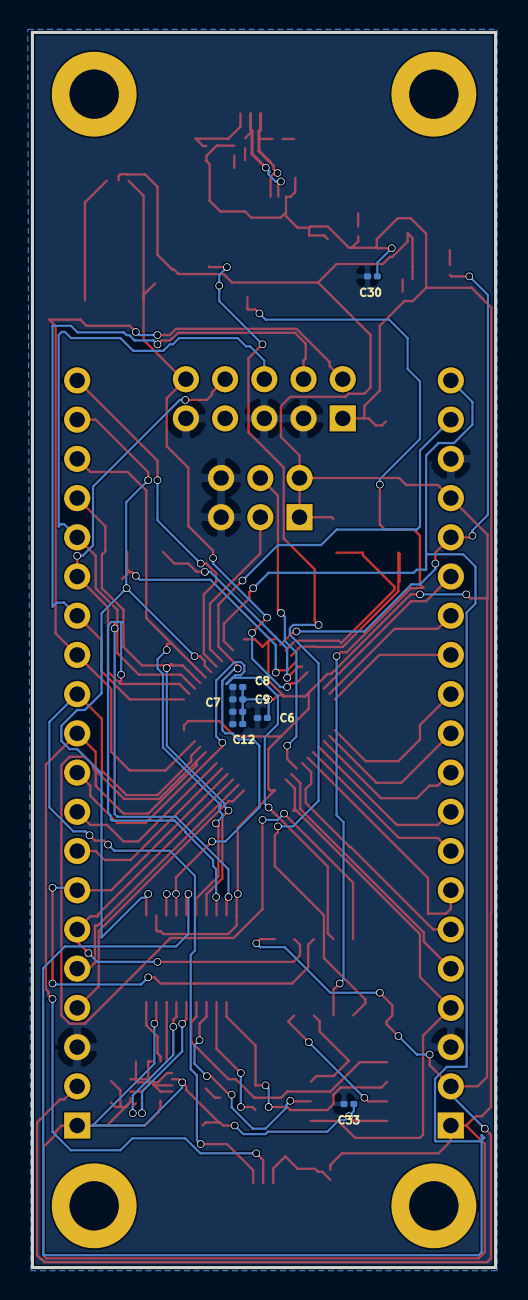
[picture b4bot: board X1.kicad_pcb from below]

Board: 2 copper layers, 30.0 x 80.0 mm, 61 parts (7 on the bottom side), 65 nets.
